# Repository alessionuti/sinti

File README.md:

# Sinti
## Eurorack modules
* Adsrt: Digital ADSR envelope and trapezoid generator
* Eugenio: Euclidean sequencer
* Quanto: CV quantizer
* Teremino: Eurorack version of the OpenTheremin V4

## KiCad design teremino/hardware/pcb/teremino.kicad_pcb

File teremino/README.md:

# Teremino
## Eurorack version of the OpenTheremin V4

### Hardware
This is a version of the OpenTheremin V4 PCB for Eurorack, including audio & CV output jacks and, a standard 8x2 power connector, a hardware button, and a ISP programming interface for the ATMEGA 328P microcontroller.

In the `panel/` folder you can find `.stl` files for the panel and a support for the two antennas, which can be fixed to the front.

### Firmware
Download the latest firmware from https://github.com/GaudiLabs/OpenThereminV4.

For more information about the design visit http://www.gaudi.ch/OpenTheremin/.

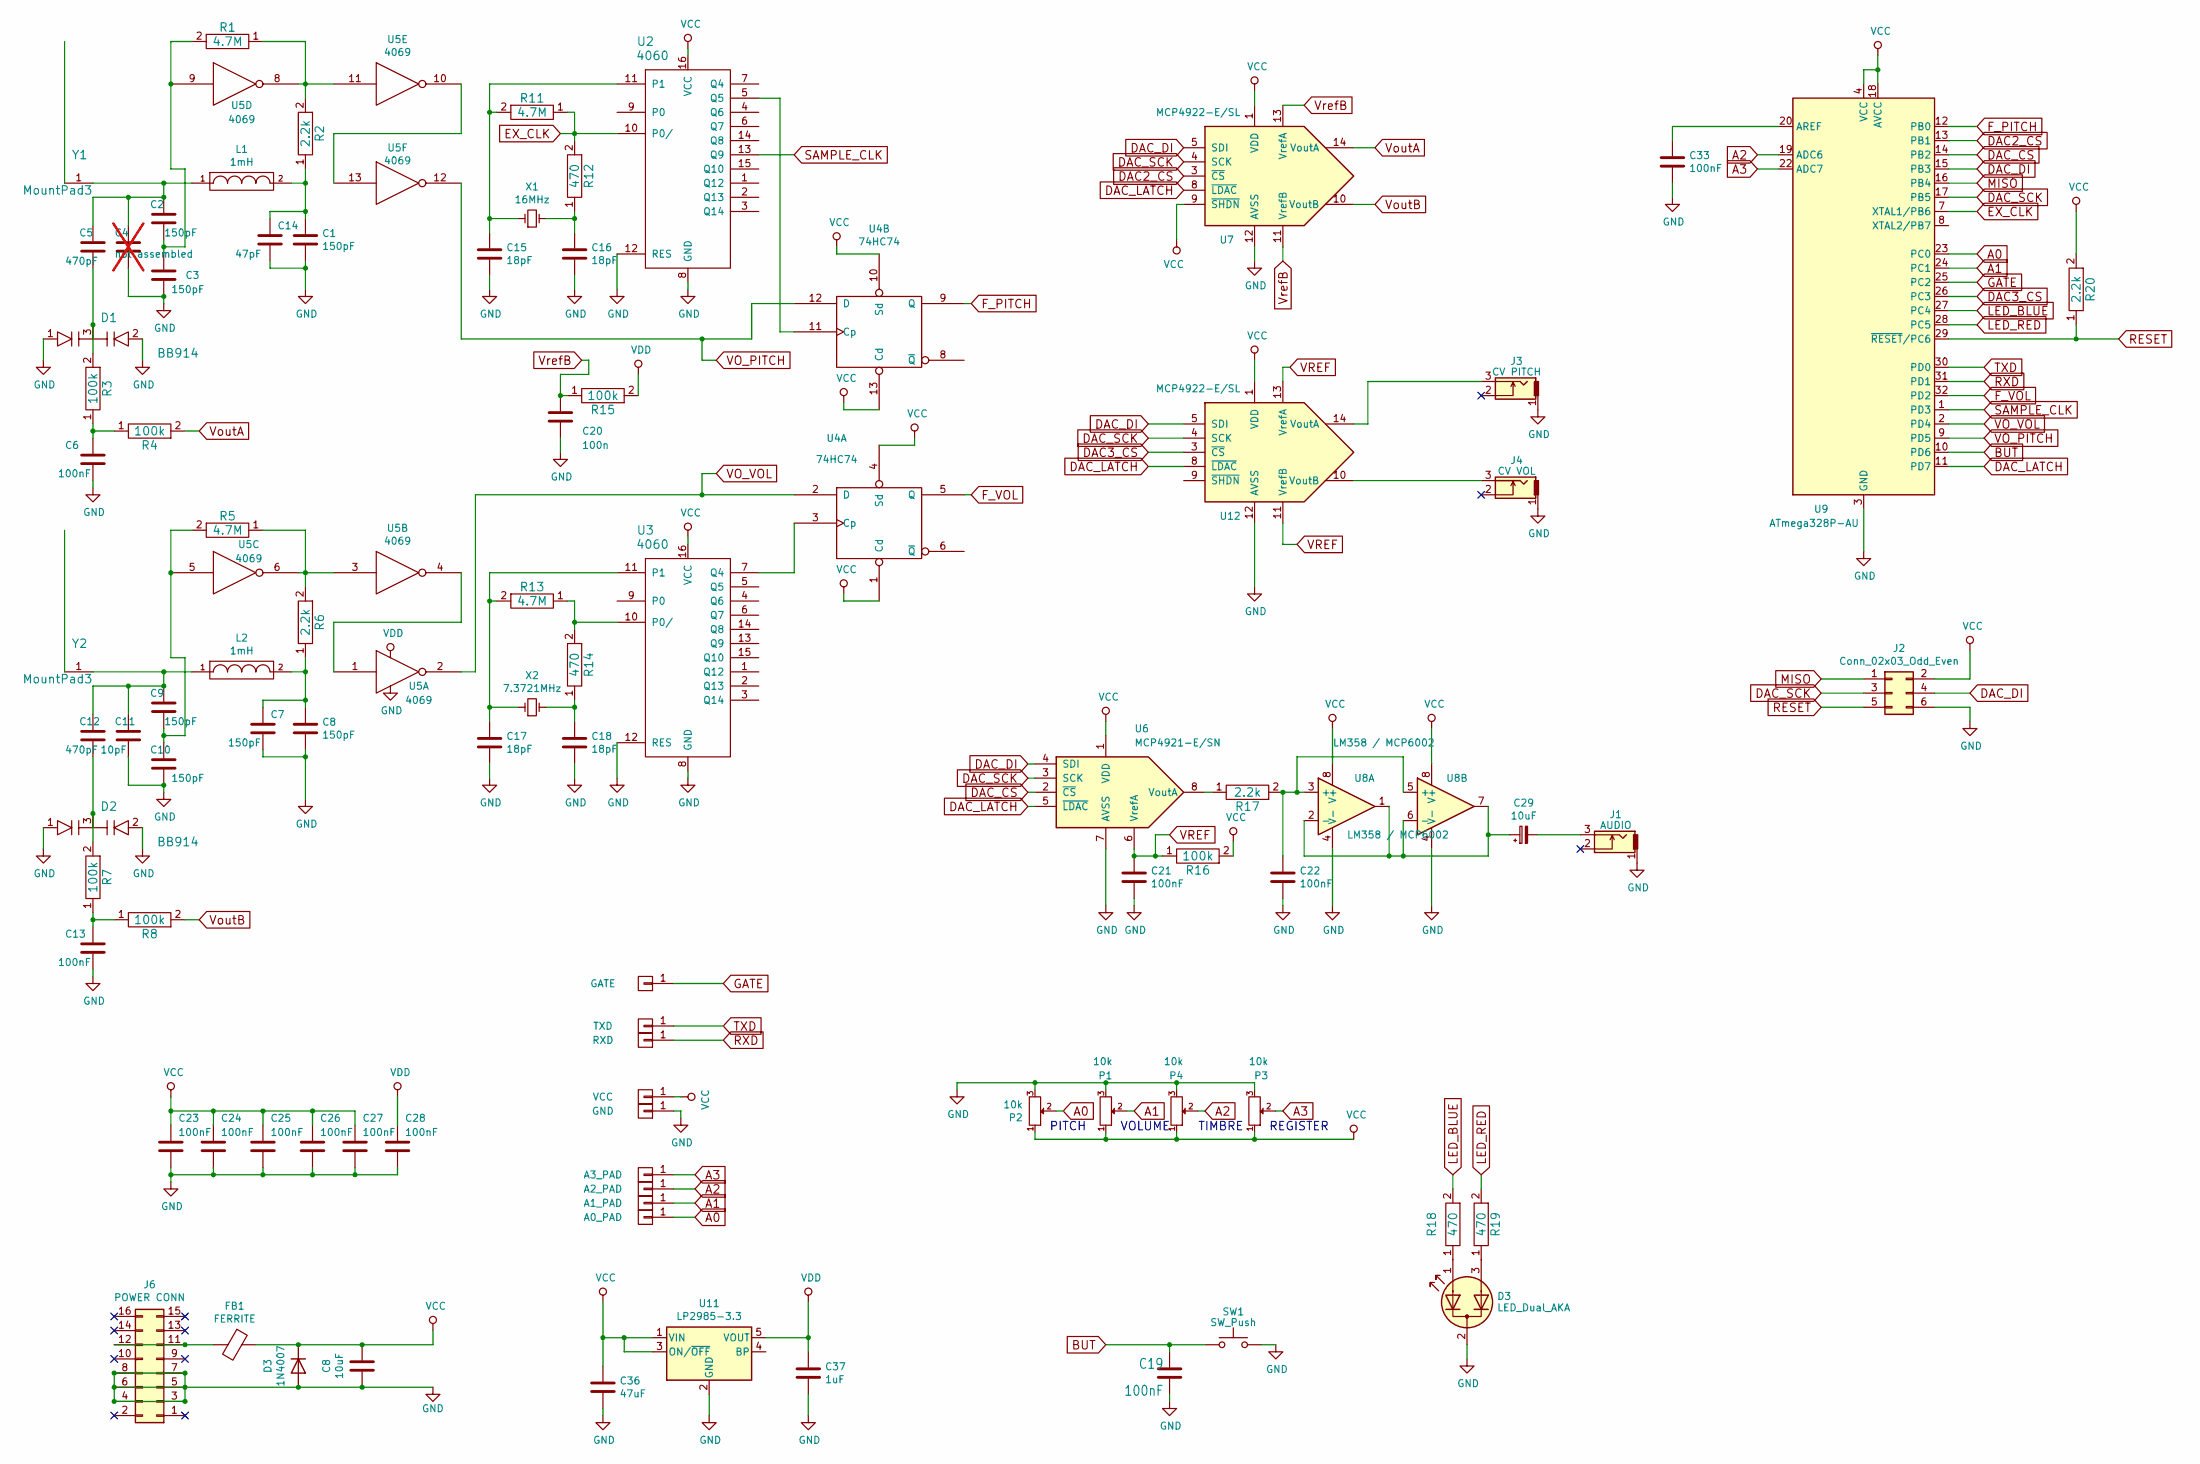
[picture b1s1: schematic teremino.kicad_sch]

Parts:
C1, C2, C3, C7, C8, C9, C10: 150pF; C_0603_1608Metric
C4: not assembled; C_0603_1608Metric; not fitted
C5, C12: 470pF; C_0603_1608Metric
C6, C13, C21, C22, C23, C24, C25, C26, C27, C28, C33: 100nF; C_0603_1608Metric
C11: 10pF; C_0603_1608Metric
C14: 47pF; C_0603_1608Metric
C15, C16, C17, C18: 18pF; C_0603_1608Metric
C19: 100nF; C_0805_2012Metric
C20: 100n; C_0603_1608Metric
C29: 10uF; C_0805_2012Metric
C36: 47uF; C_1206_3216Metric
C37: 1uF; C_0603_1608Metric
D1, D2: BB914; SOT-23
D3: 1N4007; D_1206_3216Metric
FB1: FERRITE; L_0603_1608Metric
J1: AUDIO; THONKICONN
J2: Conn_02x03_Odd_Even; PinHeader_2x03_P2.54mm_Vertical
J3: CV PITCH; THONKICONN
J4: CV VOL; THONKICONN
J6: POWER CONN; IDC-Header_2x08_P2.54mm_Vertical
L1, L2: 1mH; L_2512_6332Metric_Pad1.52x3.35mm_HandSolder
P1, P2, P3, P4: 10k; Potentiometer_Alpha_RD901F-40-00D_Single_Vertical
P5: RXD; TestPoint_Pad_1.5x1.5mm
P6: TXD; TestPoint_Pad_1.5x1.5mm
P7: GATE; TestPoint_Pad_1.5x1.5mm
P8: VCC; TestPoint_Pad_1.5x1.5mm
P9: GND; TestPoint_Pad_1.5x1.5mm
P11: A3_PAD; TestPoint_Pad_1.5x1.5mm
P12: A2_PAD; TestPoint_Pad_1.5x1.5mm
P13: A1_PAD; TestPoint_Pad_1.5x1.5mm
P14: A0_PAD; TestPoint_Pad_1.5x1.5mm
R1, R5, R11, R13: 4.7M; R_0603_1608Metric
R2, R6, R17, R20: 2.2k; R_0603_1608Metric
R3, R4, R7, R8, R15, R16: 100k; R_0603_1608Metric
R12, R14, R18, R19: 470; R_0603_1608Metric
SW1: SW_Push; SW_Push_1P1T_NO_6x6mm_H9.5mm
U2, U3: 4060; SOIC-16_3.9x9.9mm_P1.27mm
U4: 74HC74; SOIC-14_3.9x8.7mm_P1.27mm
U5: 4069; SOIC-14_3.9x8.7mm_P1.27mm
U6: MCP4921-E/SN; SOIC-8_3.9x4.9mm_P1.27mm
U7, U12: MCP4922-E/SL; SOIC-14_3.9x8.7mm_P1.27mm
U8: LM358 / MCP6002; SOIC-8_3.9x4.9mm_P1.27mm
U9: ATmega328P-AU; TQFP-32_7x7mm_P0.8mm
U11: LP2985-3.3; SOT-23-5
X1: 16MHz; Crystal_SMD_HC49-SD
X2: 7.3721MHz; Crystal_SMD_HC49-SD
Y1, Y2: MountPad3; AntennaMountHole

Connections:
A0: P2.2, P14.1, U9.23 (PC0)
A1: P1.2, P13.1, U9.24 (PC1)
A2: P4.2, P12.1, U9.19 (ADC6)
A3: P3.2, P11.1, U9.22 (ADC7)
DAC2_CS: U7.3 (~CS), U9.13 (PB1)
DAC3_CS: U9.26 (PC3), U12.3 (~CS)
DAC_CS: U6.2 (~CS), U9.14 (PB2)
DAC_DI: J2.4, U6.4 (SDI), U7.5 (SDI), U9.15 (PB3), U12.5 (SDI)
DAC_LATCH: U6.5 (~LDAC), U7.8 (~LDAC), U9.11 (PD7), U12.8 (~LDAC)
DAC_SCK: J2.3, U6.3 (SCK), U7.4 (SCK), U9.17 (PB5), U12.4 (SCK)
EX_CLK: R11.1, R12.2, U2.10 (P0/), U9.7 (XTAL1/PB6)
F_PITCH: U4.9 (Q), U9.12 (PB0)
F_VOL: U4.5 (Q), U9.32 (PD2)
GATE: P7.1, U9.25 (PC2)
GND: C1.2, C3.2, C4.2, C6.2, C7.2, C8.2, C10.2, C11.2, C13.2, C14.2, C15.2, C16.2, C17.2, C18.2, C19.2, C20.2, C21.2, C22.2, C23.2, C24.2, C25.2, C26.2, C27.2, C28.2, C33.2, C36.2, C37.2, D1.1, D1.2, D2.1, D2.2, D3.2 (K), J1.1, J2.6, J3.1, J4.1, J6.3, J6.4, J6.5, J6.6, J6.7, J6.8, P1.3, P2.3, P3.3, P4.3, P9.1, SW1.2, U2.8 (GND), U2.12 (RES), U3.8 (GND), U3.12 (RES), U4.7 (GND), U5.7 (VSS), U6.7 (AVSS), U7.12 (AVSS), U8.4 (V-), U9.3 (GND), U9.5 (GND), U9.21 (GND), U11.2 (GND), U12.12 (AVSS); also elsewhere on the board
LED_BLUE: R18.2, U9.27 (PC4)
LED_RED: R19.2, U9.28 (PC5)
MISO: J2.1, U9.16 (PB4)
unnamed: C1.1, C14.1, L1.2, R2.1
unnamed: C2.1, C4.1, C5.1, L1.1, Y1.1
unnamed: C2.2, C3.1, R1.2, U5.9
unnamed: C5.2, D1.3, R3.2
unnamed: C6.1, R3.1, R4.1
unnamed: C9.2, C10.1, R5.2, U5.5
unnamed: C9.1, C11.1, C12.1, L2.1, Y2.1
unnamed: C12.2, D2.3, R7.2
unnamed: C13.1, R7.1, R8.1
unnamed: C16.1, R12.1, X1.2
unnamed: C18.1, R14.1, X2.2
unnamed: C29.2, J1.3
unnamed: D3.3 (A2), R19.1
unnamed: FB1.2, J6.11, J6.12
unnamed: R1.1, R2.2, U5.8, U5.11
unnamed: R5.1, R6.2, U5.3, U5.6
unnamed: C15.1, R11.2, U2.11 (P1), X1.1
unnamed: U2.5 (Q5), U4.11 (Cp)
unnamed: R13.1, R14.2, U3.10 (P0/)
unnamed: C17.1, R13.2, U3.11 (P1), X2.1
unnamed: U3.7 (Q4), U4.3 (Cp)
unnamed: U5.1, U5.4
unnamed: U5.10, U5.13
unnamed: R17.1, U6.8 (VoutA)
unnamed: C22.1, R17.2, U8.3 (+), U8.5 (+)
unnamed: C29.1, U8.1, U8.2 (-), U8.6 (-), U8.7
unnamed: C33.1, U9.20 (AREF)
unnamed: J3.3, U12.14 (VoutA)
unnamed: J4.3, U12.10 (VoutB)
RESET: J2.5, R20.1, U9.29 (~RESET/PC6)
RXD: P5.1, U9.31 (PD1)
SAMPLE_CLK: U2.13 (Q9), U9.1 (PD3)
TXD: P6.1, U9.30 (PD0)
VDD: C28.1, C37.1, R15.2, U5.14 (VDD), U11.5 (VOUT)
VO_PITCH: U4.12 (D), U5.12, U9.9 (PD5)
VO_VOL: U4.2 (D), U5.2, U9.2 (PD4)
VREF: C21.1, R16.1, U6.6 (VrefA), U12.11 (VrefB), U12.13 (VrefA)
VoutA: R4.2, U7.14 (VoutA)
VoutB: R8.2, U7.10 (VoutB)
VrefB: C20.1, R15.1, U7.11 (VrefB), U7.13 (VrefA)

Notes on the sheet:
TIMBRE
REGISTER
PITCH
VOLUME

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
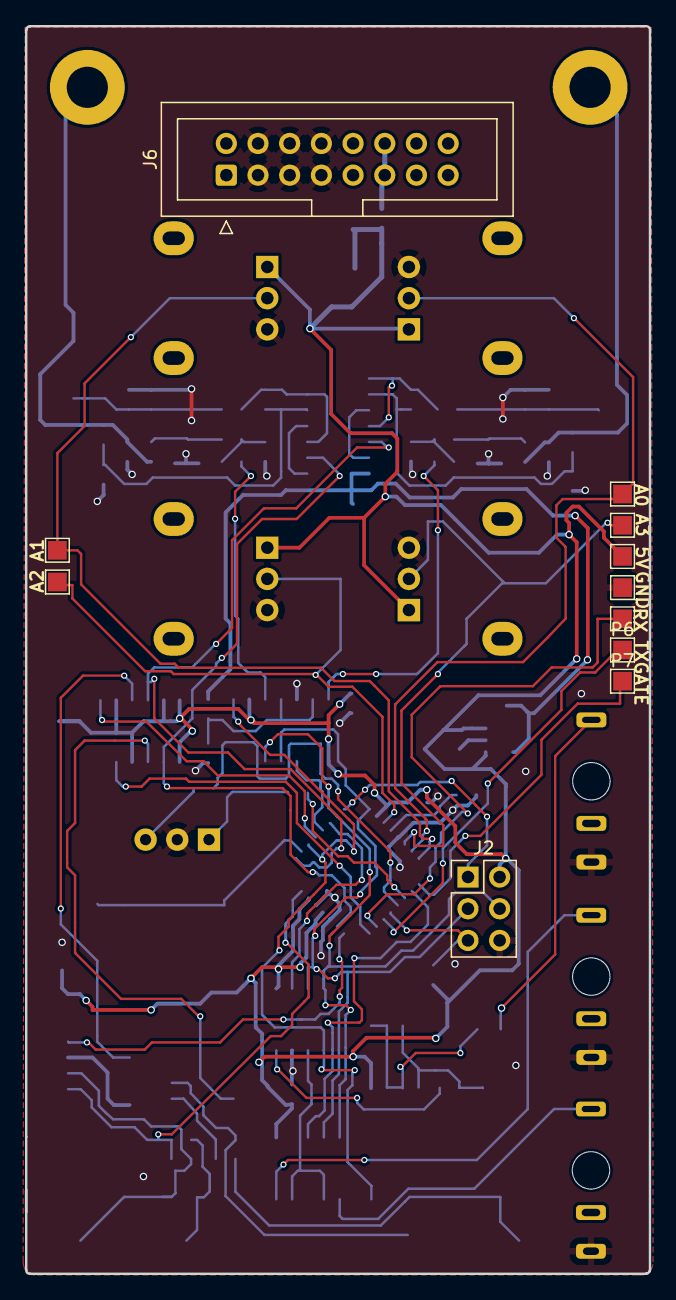
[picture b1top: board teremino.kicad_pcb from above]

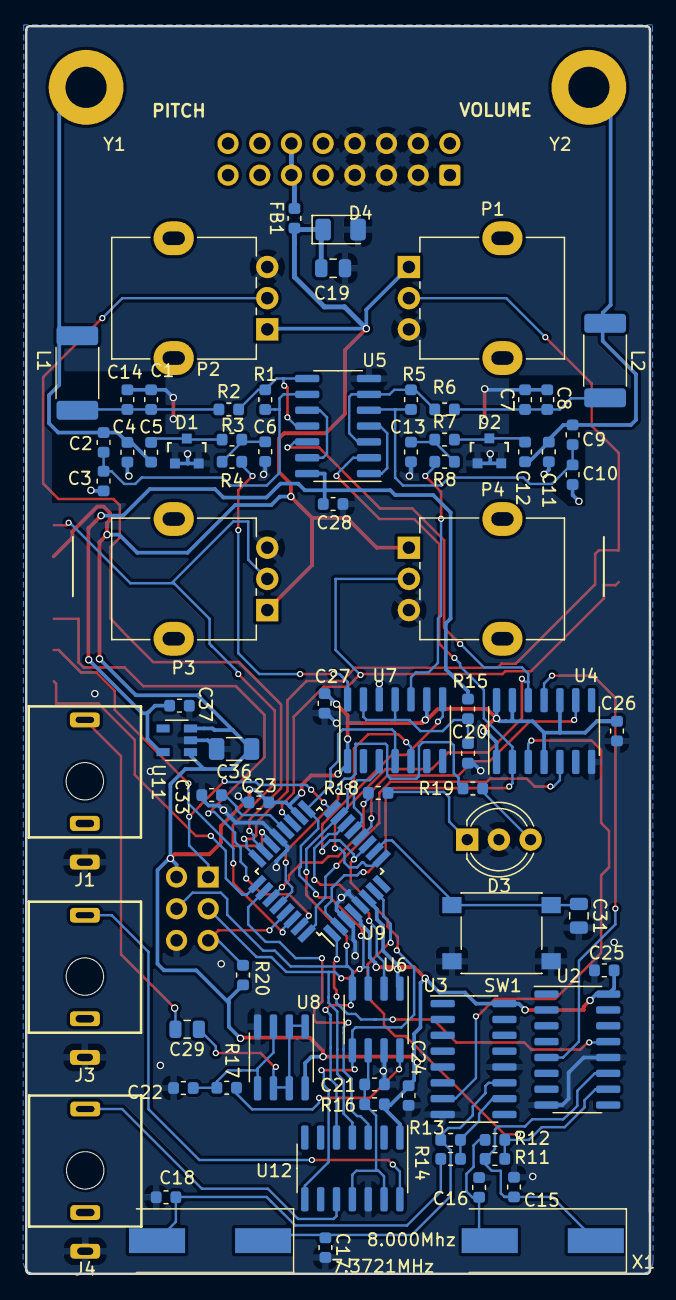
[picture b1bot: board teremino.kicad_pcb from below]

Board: 2 copper layers, 50.0 x 100.0 mm, 91 parts (78 on the bottom side), 62 nets.

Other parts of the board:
C31: 100nF; C_0805_2012Metric
D4: 1N4007; D_1206_3216Metric

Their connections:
GND: C31.2, D4.2 (A); also elsewhere on the board

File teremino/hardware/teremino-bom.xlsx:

Qty | Reference(s) | Value | Footprint
2 | U2,U3 | 74HC4060D | SOIC-16_N
1 | U4 | 74HC74D | SOIC-14_N
1 | U5 | HEF4069UBT | SOIC-14_N
1 | U6 | MCP4921T-E/SN DAC Sgl 12-bit SPI int | SOIC-08_N
2 | U7, U12 | MCP4922T-E/SL DAC Dual 12-bit SPI int | SOIC-14_N
1 | U8 | MCP6002T-I/SN OpAmp Dual 1.8V 1MHz | SOIC-08_N
1 | U9 | ATMEGA328P-AU 8-bit Microcontrollers | TQFP-32_7x7mm_P0.8mm
1 | U11 | LP2985-33DBV LDO Voltage Regulators 3.3V, 150-mA | SOT-23-5
2 | D1,D2 | BB 914 E6327 Varactor Diodes 50mA Silicn | SOT-23
1 | D3 | BiColor LED common cathode on central pin | DualLED
1 | D4 | 1N4007 | 1206
1 | FB1 | Ferrite Bead | 0603
1 | X1 | Crystals 16.000MHz +/-30ppm 18pF | HC49-SD
1 | X2 | Crystals 7.37280MHz +/-30ppm 18pF | HC49-SD
2 | L1,L2 | CC453232A-102KL Coil, 1mH UH 10%, 40 Ohms | COIL
7 | C1,C2,C3,C7,C8,C9,C10 | 150pF 50V NP0 5% | C0603
2 | C5,C12 | 470pF 50V NP0 5% | C0603
13 | C6,C13,C20,C21,C22,C23, C24,C25,C26,C27,C28,C31,C33 | 100nF 25V X7R 10% | C0603
1 | C19, C29 | 10uF 16V X5R 10% | C0603
1 | C14 | 47pF 50V NP0 5% | C0603
1 | C11 | 10pF 50V NP0 5% | C0603
0 | C4 | DO NOT POPULATE | C0603
4 | C15,C16,C17,C18 | 18pF 16 V NP0 5% | C0603
1 | C36 | 47uF 16V X5R 10% | C1206
1 | C37 | 1uF 16V X5R 10% | C0603
4 | R1,R5,R11,R13 | 4.7M | R0603
4 | R12,R14,R18,R19 | 470R | R0603
6 | R3,R4,R7,R8,R15,R16 | 100k | R0603
4 | R2,R6,R17,R20 | 2.2k | R0603
4 | P1,P2,P3,P4 | B10k | POTENTIOMETER_9MM
3 | J1, J3,J4 | AUDIO, CV PITCH, CV VOL | PJ301M-12 Thonkiconn Jack
2 | Y1, Y2 | ANTENNA MOUNT | MOUNT HOLE
1 | J2 | ISP CONN | HEADER2X3
1 | J6 | POWER CONN | HEADER2X5 SHROUDED
1 | SW1 | BUTTON | BUTTON SMD 6x6mm

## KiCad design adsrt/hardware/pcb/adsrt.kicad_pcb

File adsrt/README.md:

# Adsrt
## Digital ADSR envelope and trapezoid generator

### Acknowledgements
Based on GMSN Pure ADSR by [Rob Spencer](https://github.com/robgmsn).

Improvements:
- envelope now returns exactly to zero after release
- A, D, R knobs are now linear with time and ranges are adjustable
- logic goes to the correct phase when switching out of trapz mode
- knob order in trapz mode is attack, on, off, release, so that attack and release knobs are the same in all modes
- attack and release are linear in trapz mode, exp in ADSR/AR modes
- better control of short trapz on/off times (useful to create shaped audio frequency oscillations)

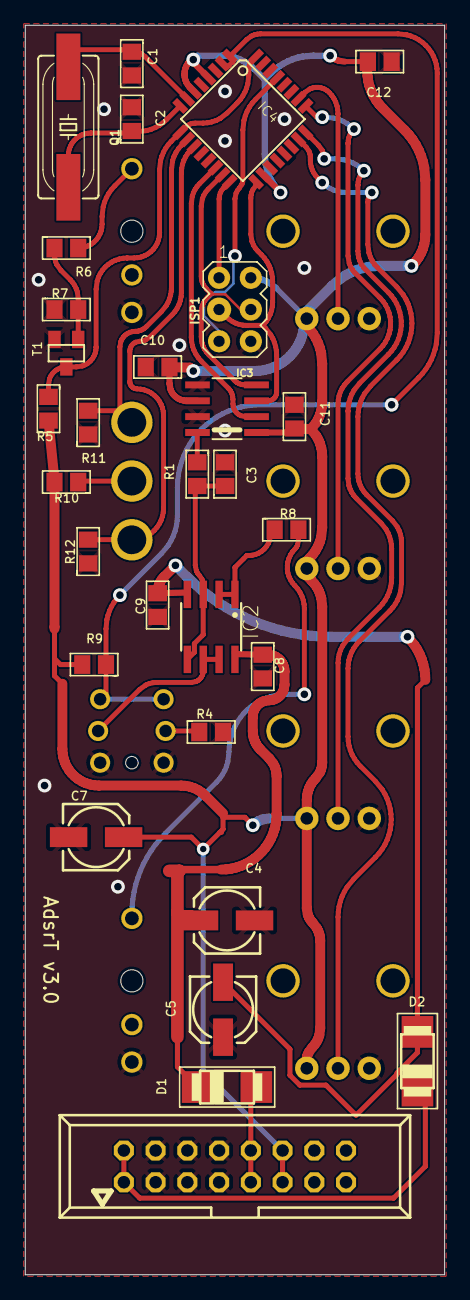
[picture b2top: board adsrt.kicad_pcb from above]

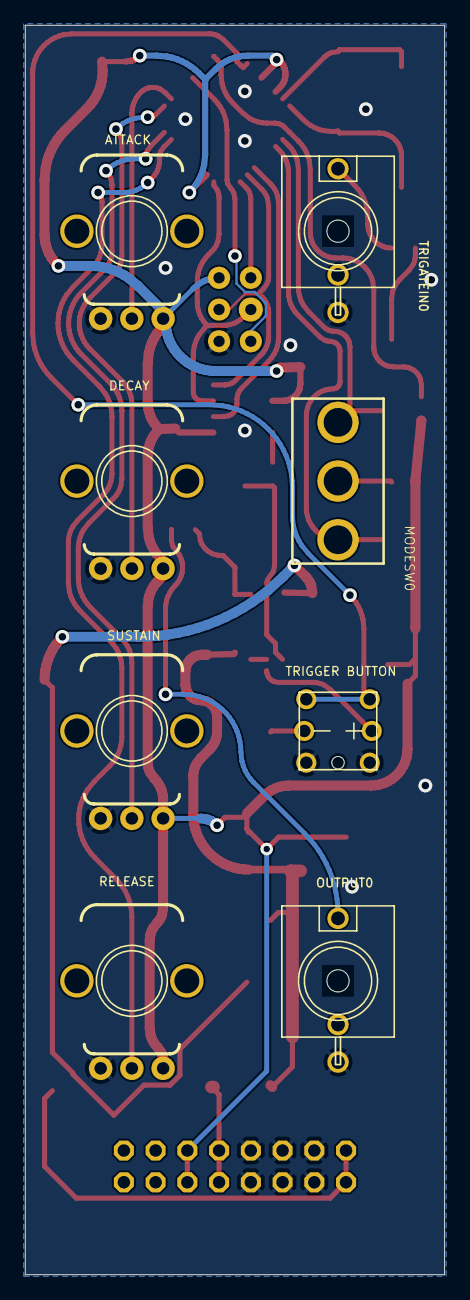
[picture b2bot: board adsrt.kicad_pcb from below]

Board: 2 copper layers, 33.6 x 100.0 mm, 38 parts (8 on the bottom side), 30 nets.

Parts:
ATTACK0: 100k; POTENTIOMETER_9MM
C1, C2: 22p; C0805
C3, C8, C9, C10, C11, C12: 100nF; C0805
C4, C5, C7: 10u; 153CLV-0505
D1, D2: STTH102A; SMADIODE
DECAY0: 100k; POTENTIOMETER_9MM
IC2: OPAMP_DUALD; SO08
IC3: MCP4921; SOIC8
IC4: ATMEGA328P; TQFP32-08
ISP1: HEADER2X3-6; AVRISP
JP1: HEADER2X8; POWER_SHROUDED
MODESW0: ON_OFF_ON; TOGGLE_SW
OUTPUT0: SOCKET_MONO_3.5MMPJ301M-12; PJ301M-12
Q1: 20MHz; HC49UP
R1: 1k6; R0805
R4: 330R; R0805
R5, R9: 10k; R0805
R6, R11, R12: 100k; R0805
R7: 1M; R0805
R8, R10: 1k; R0805
RELEASE0: 100k; POTENTIOMETER_9MM
SUSTAIN0: 100k; POTENTIOMETER_9MM
T1: 2N3904; SOT23
TRIGATEIN0: SOCKET_MONO_3.5MMPJ301M-12; PJ301M-12
TRIGGER0: PB6149L-5; PB6149L

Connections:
5V: ATTACK0.P$3, C7.+, C10.1, C11.1, C12.1, DECAY0.P$3, IC3.1, IC3.6, IC4.4, IC4.6, IC4.18, ISP1.2, JP1.11, JP1.12, R5.2, R9.2, R10.2, RELEASE0.P$3, SUSTAIN0.P$3
+12V: C4.+, C8.1, D1.C, IC2.8
-12V: C5.-, C9.2, D2.A, IC2.4
B_TRIG: IC4.1, IC4.2, R9.1, TRIGGER0.1, TRIGGER0.2
CS: IC3.2, IC4.14
GND: ATTACK0.P$1, C1.2, C2.2, C3.2, C4.-, C5.+, C7.-, C8.2, C9.1, C10.2, C11.2, C12.2, DECAY0.P$1, IC3.5, IC3.7, IC4.3, IC4.5, IC4.21, ISP1.6, JP1.3, JP1.4, JP1.5, JP1.6, JP1.7, JP1.8, OUTPUT0.GND, R4.2, R7.1, R11.1, R12.1, RELEASE0.P$1, SUSTAIN0.P$1, T1.2, TRIGATEIN0.GND, TRIGGER0.3, TRIGGER0.4
MISO: IC4.16, ISP1.1
MOSI: IC3.4, IC4.15, ISP1.4
unnamed: C1.1, IC4.7, Q1.2
unnamed: C2.1, IC4.8, Q1.1
unnamed: IC3.8, R1.1
unnamed: C3.1, IC2.3, IC2.5, R1.2
unnamed: IC2.1, IC2.2, R8.1
unnamed: IC2.6, IC2.7, TRIGGER0.A
unnamed: R4.1, TRIGGER0.K
unnamed: OUTPUT0.TIP, R8.2
unnamed: MODESW0.2, R10.1
unnamed: D2.C, JP1.1, JP1.2
unnamed: R6.1, R7.2, T1.1
unnamed: R6.2, TRIGATEIN0.TIP
unnamed: D1.A, JP1.9, JP1.10
POT_A: ATTACK0.P$2, IC4.26
POT_D: DECAY0.P$2, IC4.25
POT_R: IC4.23, RELEASE0.P$2
POT_S: IC4.24, SUSTAIN0.P$2
RST: IC4.29, ISP1.5
SCK: IC3.3, IC4.17, ISP1.3
T1: IC4.10, MODESW0.3, R11.2
T2: IC4.11, MODESW0.1, R12.2
TRIG: IC4.9, IC4.32, R5.1, T1.3

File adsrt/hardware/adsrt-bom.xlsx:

Qty | Reference(s) | Value | Footprint
2 | C1, C2 | 22p | C0805
1 | C3 | 470p | C0805
5 | C8, C9, C10, C11, C12 | 100n | C0805
3 | C4, C5, C7 | 10u | 153CLV-0505
2 | D1, D2 | STTH102A | SMADIODE
1 | IC2 | OPAMP_DUALD_TL072 | SO08
1 | IC3 | DAC_SINGLE_12B_MCP4921 | SOIC8
1 | IC4 | ATMEGA328P | TQFP32-08
1 | Q1 | 20MHz CRYSTAL | HC49UP
1 | R4 | 330R | R0805
3 | R1, R5, R9 | 10k | R0805
3 | R6, R11, R12 | 100k | R0805
1 | R7 | 1M | R0805
2 | R8, R10 | 1k | R0805
1 | ATTACK0 | B100k | POTENTIOMETER_9MM
1 | DECAY0 | B100k | POTENTIOMETER_9MM
1 | RELEASE0 | B100k | POTENTIOMETER_9MM
1 | SUSTAIN0 | B100k | POTENTIOMETER_9MM
1 | T1 | MMBT3904 | SOT23
1 | OUTPUT0 | SOCKET_MONO_3.5MMPJ301M-12 | PJ301M-12 Thonkiconn Jack
1 | TRIGATEIN0 | SOCKET_MONO_3.5MMPJ301M-12 | PJ301M-12 Thonkiconn Jack
1 | ISP1 | AVR ISP CONN | HEADER2X3
1 | JP1 | POWER CONN | HEADER2X8
1 | MODESW0 | MODE SWITCH ON-OFF-ON | SWITCH_TOGGLE_SP3T
1 | TRIGGER0 | TRIGGER BUTTON LED | PB6149L

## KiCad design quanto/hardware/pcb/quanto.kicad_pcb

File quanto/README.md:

# Quanto
## CV quantizer
See `manual/` for full documentation.

### Acknowledgements
Based on GMSN Pure Quantiser by [Rob Spencer](https://github.com/robgmsn).

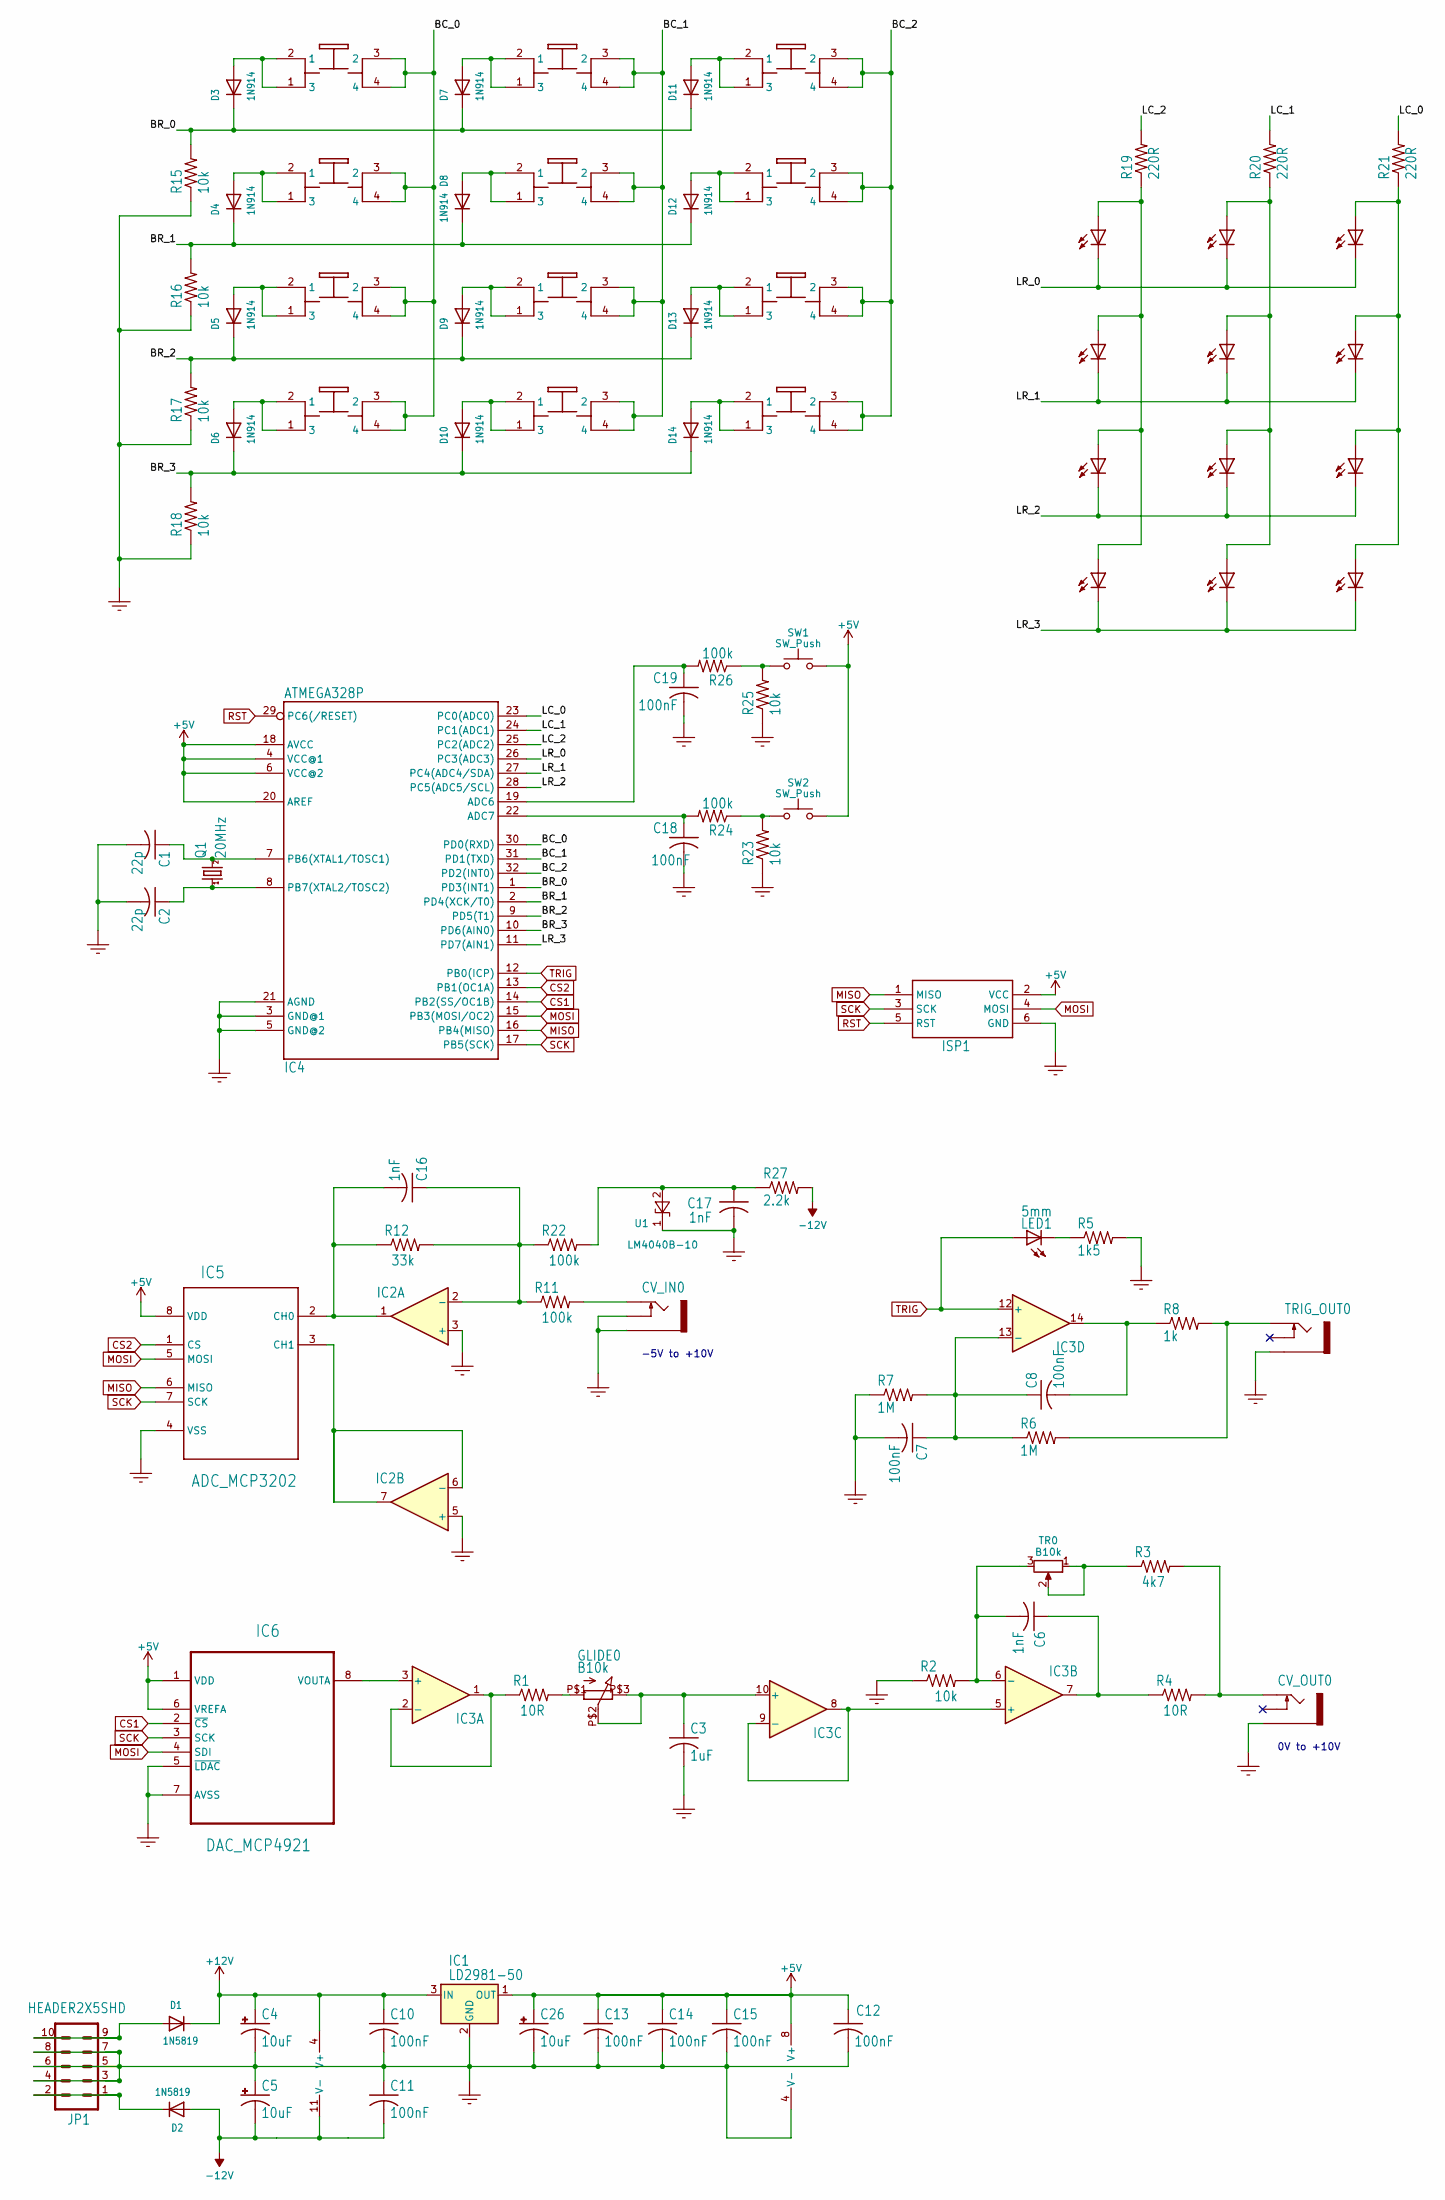
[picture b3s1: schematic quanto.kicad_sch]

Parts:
C1, C2: 22p; C0805
C3: 1uF; C0805
C4, C5, C26: 10uF; 153CLV-0505
C6, C16, C17: 1nF; C0805
C7, C8, C10, C11, C12, C13, C14, C15: 100nF; C0805
C18, C19: 100nF; C_0805_2012Metric
CV_IN0: SOCKET_MONO_3.5MMPJ301M-12; PJ301M-12
CV_OUT0: SOCKET_MONO_3.5MMPJ301M-12; PJ301M-12
D1, D2: 1N5819; SMADIODE
D3, D4, D5, D6, D7, D8, D9, D10, D11, D12, D13, D14: 1N914; D_SOD-123
GLIDE0: B10k; POTENTIOMETER_9MM
IC1: LD2981-50; SOT-89-3
IC2: MCP602; SO08
IC3: TL074; SO14
IC4: ATMEGA328P; TQFP32-08
IC5: ADC_MCP3202; SOIC--8
IC6: DAC_MCP4921; SOIC8
ISP1: HEADER2X3-6; AVRISP
JP1: HEADER2X5SHD; 2X5-SHROUDED
LED1: 5mm; LED5MM
Q1: 20MHz; HC49UP
R1, R4: 10R; R0805
R2, R15, R16, R17, R18: 10k; R0805
R3: 4k7; R0805
R5: 1k5; R0805
R6, R7: 1M; R0805
R8: 1k; R0805
R11, R22: 100k; R0805
R12: 33k; R0805
R19, R20, R21: 220R; R0805
R23, R25: 10k; R_0805_2012Metric
R24, R26: 100k; R_0805_2012Metric
R27: 2.2k; R_0805_2012Metric
SW1, SW2: SW_Push; SW_Push_1P1T_NO_6x6mm_H9.5mm
TR0: B10k; Potentiometer_Bourns_3269W_Vertical
TRIG_OUT0: SOCKET_MONO_3.5MMPJ301M-12; PJ301M-12
U1: LM4040B-10; SOT-23
UNK1, UNK2, UNK3, UNK4, UNK5, UNK6, UNK7, UNK8, UNK9, UNK10, UNK11, UNK12: PB6149L-5; PB6149L

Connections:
+5V: C12.1, C13.1, C14.1, C15.1, C26.+, IC1.1 (OUT), IC2.8 (V+), IC4.4 (VCC@1), IC4.6 (VCC@2), IC4.18 (AVCC), IC4.20 (AREF), IC5.8 (VDD), IC6.1 (VDD), IC6.6 (VREFA), ISP1.2 (VCC), SW1.2, SW2.2
+12V: C4.+, C10.1, D1.C, IC1.3 (IN), IC3.4 (V+)
-12V: C5.-, C11.2, D2.A, IC3.11 (V-), R27.2
/BC_0: IC4.30 (PD0(RXD)), UNK1.3 (2), UNK1.4, UNK2.3 (2), UNK2.4, UNK3.3 (2), UNK3.4, UNK4.3 (2), UNK4.4
/BC_1: IC4.31 (PD1(TXD)), UNK5.3 (2), UNK5.4, UNK6.3 (2), UNK6.4, UNK7.3 (2), UNK7.4, UNK8.3 (2), UNK8.4
/BC_2: IC4.32 (PD2(INT0)), UNK9.3 (2), UNK9.4, UNK10.3 (2), UNK10.4, UNK11.3 (2), UNK11.4, UNK12.3 (2), UNK12.4
/BR_0: D3.1 (K), D7.1 (K), D11.1 (K), IC4.1 (PD3(INT1)), R15.2
/BR_1: D4.1 (K), D8.1 (K), D12.1 (K), IC4.2 (PD4(XCK/T0)), R16.2
/BR_2: D5.1 (K), D9.1 (K), D13.1 (K), IC4.9 (PD5(T1)), R17.2
/BR_3: D6.1 (K), D10.1 (K), D14.1 (K), IC4.10 (PD6(AIN0)), R18.2
/LC_0: IC4.23 (PC0(ADC0)), R21.2
/LC_1: IC4.24 (PC1(ADC1)), R20.2
/LC_2: IC4.25 (PC2(ADC2)), R19.2
/LR_0: IC4.26 (PC3(ADC3)), UNK1.K (C), UNK5.K (C), UNK9.K (C)
/LR_1: IC4.27 (PC4(ADC4/SDA)), UNK2.K (C), UNK6.K (C), UNK10.K (C)
/LR_2: IC4.28 (PC5(ADC5/SCL)), UNK3.K (C), UNK7.K (C), UNK11.K (C)
/LR_3: IC4.11 (PD7(AIN1)), UNK4.K (C), UNK8.K (C), UNK12.K (C)
CS1: IC4.14 (PB2(SS/OC1B)), IC6.2 (~CS)
CS2: IC4.13 (PB1(OC1A)), IC5.1 (CS)
GND: C1.2, C2.2, C3.2, C4.-, C5.+, C7.2, C10.2, C11.1, C12.2, C13.2, C14.2, C15.2, C17.2, C18.2, C19.2, C26.-, CV_IN0.GND (SLEEVE), CV_IN0.NORM (SWITCH), CV_OUT0.GND (SLEEVE), IC1.2 (GND), IC2.3 (+), IC2.4 (V-), IC2.5 (+), IC4.3 (GND@1), IC4.5 (GND@2), IC4.21 (AGND), IC5.4 (VSS), IC6.5 (~LDAC), IC6.7 (AVSS), ISP1.6 (GND), JP1.3, JP1.4, JP1.5, JP1.6, JP1.7, JP1.8, R2.1, R5.2, R7.1, R15.1, R16.1, R17.1, R18.1, R23.1, R25.1, TRIG_OUT0.GND (SLEEVE), U1.1 (K)
MISO: IC4.16 (PB4(MISO)), IC5.6 (MISO), ISP1.1 (MISO)
MOSI: IC4.15 (PB3(MOSI/OC2)), IC5.5 (MOSI), IC6.4 (SDI), ISP1.4 (MOSI)
unnamed: C6.1, IC3.7, R4.1
unnamed: C8.2, IC3.14, R8.1
unnamed: CV_IN0.TIP, R11.2
unnamed: CV_OUT0.TIP, R3.2, R4.2
unnamed: D1.A, JP1.9, JP1.10
unnamed: D2.C, JP1.1, JP1.2
unnamed: D3.2 (A), UNK1.1 (3), UNK1.2 (1)
unnamed: D4.2 (A), UNK2.1 (3), UNK2.2 (1)
unnamed: D5.2 (A), UNK3.1 (3), UNK3.2 (1)
unnamed: D6.2 (A), UNK4.1 (3), UNK4.2 (1)
unnamed: D7.2 (A), UNK5.1 (3), UNK5.2 (1)
unnamed: D8.2 (A), UNK6.1 (3), UNK6.2 (1)
unnamed: D9.2 (A), UNK7.1 (3), UNK7.2 (1)
unnamed: D10.2 (A), UNK8.1 (3), UNK8.2 (1)
unnamed: D11.2 (A), UNK9.1 (3), UNK9.2 (1)
unnamed: D12.2 (A), UNK10.1 (3), UNK10.2 (1)
unnamed: D13.2 (A), UNK11.1 (3), UNK11.2 (1)
unnamed: D14.2 (A), UNK12.1 (3), UNK12.2 (1)
unnamed: GLIDE0.P$1 (1), R1.2
unnamed: C3.1, GLIDE0.P$2 (2), GLIDE0.P$3 (3), IC3.10 (+)
unnamed: C16.1, IC2.2 (-), R11.1, R12.2, R22.1
unnamed: IC2.6 (-), IC2.7, IC5.3 (CH1)
unnamed: IC3.3 (+), IC6.8 (VOUTA)
unnamed: IC3.1, IC3.2 (-), R1.1
unnamed: IC3.5 (+), IC3.8, IC3.9 (-)
unnamed: C6.2, IC3.6 (-), R2.2, TR0.3
unnamed: C7.1, C8.1, IC3.13 (-), R6.1, R7.2
unnamed: C19.1, IC4.19 (ADC6), R26.2
unnamed: C18.1, IC4.22 (ADC7), R24.2
unnamed: C1.1, IC4.7 (PB6(XTAL1/TOSC1)), Q1.2
unnamed: C2.1, IC4.8 (PB7(XTAL2/TOSC2)), Q1.1
unnamed: C16.2, IC2.1, IC5.2 (CH0), R12.1
unnamed: LED1.K (C), R5.1
unnamed: R3.1, TR0.1, TR0.2
unnamed: R6.2, R8.2, TRIG_OUT0.TIP
unnamed: R19.1, UNK1.A, UNK2.A, UNK3.A, UNK4.A
unnamed: R20.1, UNK5.A, UNK6.A, UNK7.A, UNK8.A
unnamed: R21.1, UNK9.A, UNK10.A, UNK11.A, UNK12.A
unnamed: R23.2, R24.1, SW2.1
unnamed: R25.2, R26.1, SW1.1
unnamed: C17.1, R22.2, R27.1, U1.2 (A)
RST: IC4.29 (PC6(/RESET)), ISP1.5 (RST)
SCK: IC4.17 (PB5(SCK)), IC5.7 (SCK), IC6.3 (SCK), ISP1.3 (SCK)
TRIG: IC3.12 (+), IC4.12 (PB0(ICP)), LED1.A

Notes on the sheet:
0V to +10V
-5V to +10V

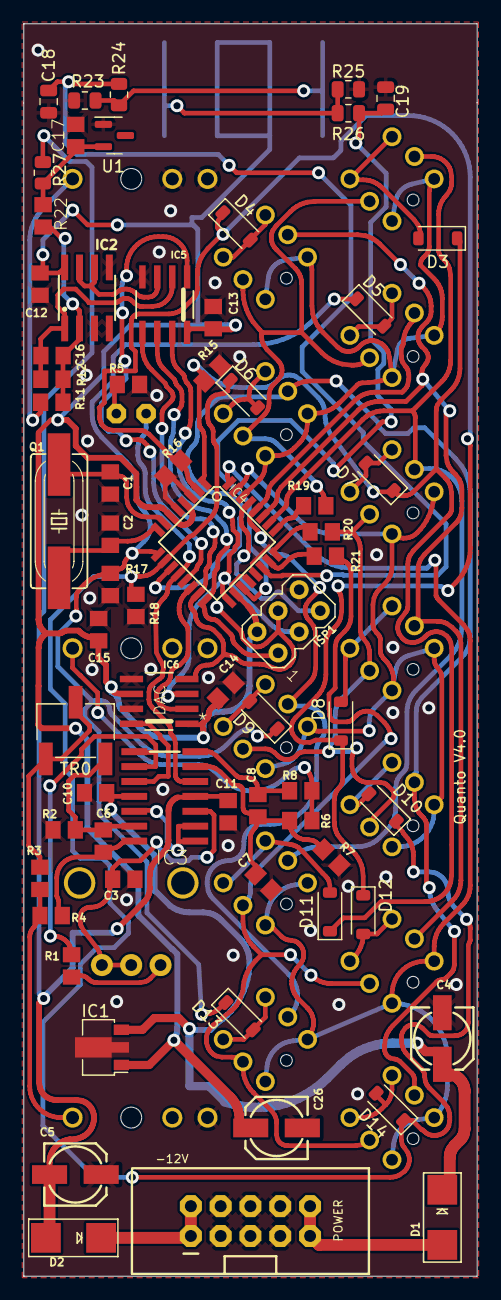
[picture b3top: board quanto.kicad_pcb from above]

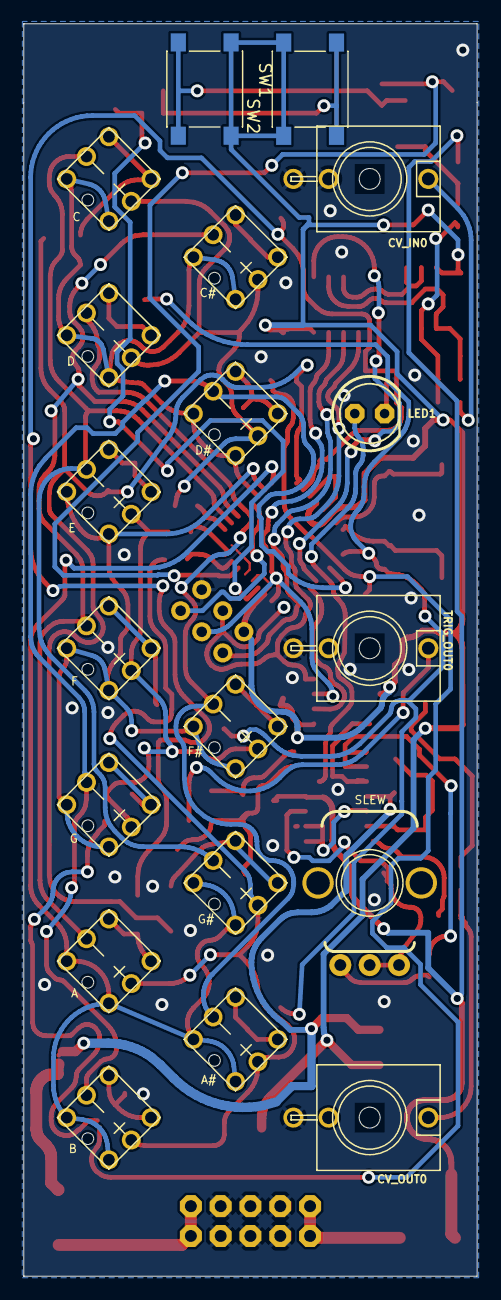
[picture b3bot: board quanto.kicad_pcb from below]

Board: 2 copper layers, 38.6 x 106.7 mm, 86 parts (19 on the bottom side), 66 nets.

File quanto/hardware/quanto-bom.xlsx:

Qty | Reference(s) | Value | Footprint
2 | C1, C2 | 22p | C0805
2 | C6, C16 | 1nF | C0805
10 | C3, C7, C8, C10, C11, C12, C13, C14, C15, C18, C19 | 100nF | C0805
1 | C3 | 1uF | C0805
3 | C4, C5, C26 | 10uF | 153CLV-0505
2 | D1, D2 | 1N5819 | SOD-123
12 | D3, D4, D5, D6, D7, D8, D9, D10, D11, D12, D13, D14 | 1N914 | SOD-123
1 | IC1 | LD2981-50 | SOT-89
1 | IC2 | MCP6002 | SOIC-08
1 | IC3 | TL074 | SOIC-14
1 | IC4 | ATMEGA328P | TQFP32-08
1 | IC5 | MCP3202 | SOIC-08
1 | IC6 | MCP4921 | SOIC-08
1 | LED1 | LED 3mm | LED THT 3mm
1 | Q1 | 20MHz CRYSTAL | HC49UP
1 | U1 | LM4040B-10 | SOT-23
2 | R1, R4 | 10R | R0805
1 | R2 | 10k | R0805
1 | R3 | 4.7k | R0805
1 | R5 | 1k5 | R0805
2 | R6, R7 | 1M | R0805
1 | R8 | 1k | R0805
4 | R11, R22, R24, R26 | 100k | R0805
1 | R12 | 33k | R0805
6 | R15, R16, R17, R18, R23, R25 | 10k | R0805
3 | R19, R20, R21 | 220R | R0805
1 | R27 | 2.2k | R0805
2 | SW1, SW2 | OCTAVE BUTTON | SW_Push_1P1T_NO_6x6mm_SMD
1 | TR0 | B10k | TRIMMER_SMD
1 | GLIDE0 | B10k | POTENTIOMETER_9MM
1 | CV_IN0 | SOCKET_MONO_3.5MMPJ301M-12 | PJ301M-12 Thonkiconn Jack
1 | CV_OUT0 | SOCKET_MONO_3.5MMPJ301M-12 | PJ301M-12 Thonkiconn Jack
1 | TRIG_OUT0 | SOCKET_MONO_3.5MMPJ301M-12 | PJ301M-12 Thonkiconn Jack
1 | ISP1 | AVR ISP CONN | HEADER2X3
1 | JP1 | POWER CONN | HEADER2X5 SHROUDED
12 | UNK1, UNK2, UNK3, UNK4, UNK5, UNK6, UNK7, UNK8, UNK9, UNK10, UNK11, UNK12 | PB6149L | SWITCH_PUSHBUTTON_LED
